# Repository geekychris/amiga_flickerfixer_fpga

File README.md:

# Amiga DENISE Flicker Fixer

An FPGA-based flicker fixer for the Commodore Amiga that reads digital RGB directly from the Super DENISE (8373 ECS) chip and outputs progressive 720p HDMI video.

**Target Platform:** Sipeed Tang Primer 20K (Gowin GW2A-LV18PG256C8/I7)

## Overview

The Amiga's native video output is 15 kHz interlaced (or non-interlaced), which most modern displays cannot accept. This flicker fixer captures the 12-bit digital RGB output from DENISE before it reaches the analog video DAC, stores fields in a DDR3 frame buffer, performs weave deinterlacing, scales the image to 720p, and outputs progressive HDMI.

Key features:
- Direct digital capture from DENISE pins (no analog conversion artifacts)
- Supports all ECS video modes: lores, hires, and superhires
- PAL and NTSC auto-detection
- Interlaced and non-interlaced mode support
- Weave deinterlacing (field merging) for flicker-free interlaced display
- Line doubling for non-interlaced modes
- Nearest-neighbor scaling to 1280x720
- 720p50 output for PAL, 720p60 for NTSC (matches source frame rate)
- Test pattern fallback when no Amiga input detected
- 128 MB DDR3 frame buffer (ping-pong per field parity)

## System Architecture

```
                        Amiga Motherboard
                        ┌──────────────┐
                        │   DENISE     │
                        │   (8373)     │
                        │              │
                        │  R[3:0] ─────┼──┐
                        │  G[3:0] ─────┼──┤
                        │  B[3:0] ─────┼──┤  12-bit digital RGB
                        │  /CSYNC ─────┼──┤  + sync/clock
                        │  /ZD    ─────┼──┤
                        │  7M     ─────┼──┤
                        │  CDAC   ─────┼──┘
                        └──────────────┘
                               │
                    ┌──────────┴──────────┐
                    │  Level Shifter      │
                    │  (74LVC245 x2)      │
                    │  5V TTL → 3.3V      │
                    └──────────┬──────────┘
                               │
┌──────────────────────────────┴──────────────────────────────┐
│                   Tang Primer 20K FPGA                       │
│                                                              │
│  ┌─────────────────┐    ┌──────────────┐    ┌────────────┐  │
│  │ denise_capture   │    │ frame_buffer │    │ output_gen │  │
│  │                  │    │    _ctrl     │    │            │  │
│  │ • 28MHz sampling │───▶│              │───▶│ • 720p     │  │
│  │ • Sync separator │    │ • DDR3      │    │   timing   │  │
│  │ • Mode detection │    │   arbiter   │    │ • Weave    │  │
│  │ • Field ID       │    │ • Ping-pong │    │   deintlc  │  │
│  │ • Pixel coords   │    │   buffers   │    │ • NN scale │  │
│  └─────────────────┘    │ • Line bufs  │    └─────┬──────┘  │
│                          └──────┬───────┘          │         │
│       ┌────────┐                │           ┌──────┴──────┐  │
│       │ Amiga  │         ┌──────┴──────┐    │  DVI_TX_Top │  │
│       │  PLL   │         │   DDR3      │    │  (Gowin IP) │  │
│       │7M→28M  │         │ Controller  │    │  TMDS enc.  │  │
│       └────────┘         │ (nand2mario │    └──────┬──────┘  │
│       ┌────────┐         │  or Gowin)  │           │         │
│       │ TMDS   │         └──────┬──────┘    ┌──────┴──────┐  │
│       │  PLL   │                │           │ HDMI Output │  │
│       │27→371M │         ┌──────┴──────┐    │ (TMDS diff) │  │
│       └────────┘         │  DDR3 SDRAM │    └─────────────┘  │
│                          │  128 MB     │                     │
│                          └─────────────┘                     │
└──────────────────────────────────────────────────────────────┘
```

### Clock Domains

| Domain | Frequency | Source | Purpose |
|--------|-----------|--------|---------|
| `I_clk` | 27 MHz | Board oscillator | System reference, DDR3 PLL input |
| `clk_28m` | ~28.38/28.64 MHz | Amiga_rPLL (4x 7M) | DENISE pixel capture |
| `clk_mem` | 100 MHz | DDR3 controller PLL | Memory access |
| `pix_clk` | 74.25 MHz | TMDS_rPLL / CLKDIV | HDMI pixel output |
| `serial_clk` | ~371.25 MHz | TMDS_rPLL | HDMI TMDS serialization |

All clock domain crossings use dual-flop synchronizers (for control signals) or async FIFOs (for data streams).

### Data Flow

```
DENISE pins (5V TTL)
    │
    ▼ (level shifted to 3.3V)
┌─────────────────────────────────────┐
│ denise_capture (28 MHz domain)      │
│ • Double-flop sync all inputs       │
│ • Sample RGB at 28 MHz              │
│ • Separate CSYNC → HSYNC + VSYNC   │
│ • Count lines → PAL/NTSC detect    │
│ • Track active area via /ZD         │
│ • Output: pixel + coords + field ID │
└──────────────┬──────────────────────┘
               ▼
        [Async FIFO 28→100 MHz]
               ▼
┌─────────────────────────────────────┐
│ frame_buffer_ctrl (100 MHz domain)  │
│ • Write pixels to DDR3 field buffer │
│ • Ping-pong buffers per parity      │
│ • Read source lines into line bufs  │
│ • Priority arbitration (read > wr)  │
└──────────────┬──────────────────────┘
               ▼
        [Line buffer BSRAM]
               ▼
┌─────────────────────────────────────┐
│ output_gen (74.25 MHz domain)       │
│ • 720p timing (50Hz or 60Hz)       │
│ • Fixed-point scale computation     │
│ • Weave deinterlace (field merge)   │
│ • 4-bit → 8-bit color expansion    │
│ • Line prefetch from frame buffer   │
└──────────────┬──────────────────────┘
               ▼
┌─────────────────────────────────────┐
│ DVI_TX_Top (Gowin encrypted IP)     │
│ • 8b/10b TMDS encoding             │
│ • OSER10 serialization              │
│ • Differential output drive         │
└──────────────┬──────────────────────┘
               ▼
         HDMI connector
```

## Module Descriptions

### `flicker_fixer_top.v` — Top Level
Instantiates all modules, manages clock generation (3 PLLs), reset sequencing, clock domain crossing for control signals, and multiplexes between Amiga video and test pattern fallback.

### `denise_capture.v` — DENISE Signal Capture
Samples DENISE's 12-bit RGB output at 28 MHz (4x the 7M clock). Includes:
- **Input synchronization**: Double-flop metastability guard on all DENISE inputs
- **Composite sync separator**: Measures /CSYNC pulse widths to distinguish normal HSYNC (~4.7 us, ~132 clocks) from equalization/serration pulses (~2.35 us, ~66 clocks) during vertical sync
- **PAL/NTSC detection**: Counts lines per field (>280 = PAL, <280 = NTSC)
- **Interlace detection**: Compares consecutive field line counts (alternating 262/263 or 312/313 = interlaced)
- **Field identification**: Long frame (extra line) = odd field, short frame = even field
- **Active area detection**: Uses /ZD (zero detect) as blanking indicator to measure active pixel width and height
- **Coordinate tracking**: Outputs pixel X/Y position within the active display area

### `frame_buffer_ctrl.v` — DDR3 Frame Buffer Arbiter
Manages DDR3 memory access for writing captured pixels and reading lines for output:
- **4 field buffers** in DDR3 (ping-pong per parity): ensures the output always reads from a completed field while capture writes to another
- **Write path**: Accepts pixels from the async FIFO, computes DDR3 addresses, issues single-word writes
- **Read path**: Prefetches entire source lines into on-chip BSRAM line buffers for zero-latency output access
- **Arbitration**: Read priority (output timing is deadline-driven) over writes

Memory map (16-bit word addresses):
```
Buffer 0 (even ping):  0x000000 + line*2048 + pixel
Buffer 1 (even pong):  0x100000 + line*2048 + pixel
Buffer 2 (odd  ping):  0x200000 + line*2048 + pixel
Buffer 3 (odd  pong):  0x300000 + line*2048 + pixel
```

Each pixel stored as 16 bits: `{4'b0, R[3:0], G[3:0], B[3:0]}`

### `output_gen.v` — HDMI Output with Deinterlacing and Scaling
Generates 720p video timing and produces scaled, deinterlaced output:
- **720p50** (1980x750, HFP=440) for PAL input
- **720p60** (1650x750, HFP=110) for NTSC input
- Both use the same 74.25 MHz pixel clock

**Weave deinterlacing**: For interlaced input, the output interleaves lines from the even and odd field buffers. Even output lines read from the even field, odd output lines from the odd field. This reconstructs the full progressive frame.

**Line doubling**: For non-interlaced input, each source line maps to two consecutive output lines.

**Nearest-neighbor scaling**: Fixed-point arithmetic maps each output pixel to source coordinates. Scale factors are recomputed at each frame start based on the detected active area dimensions.

**Line prefetch**: At the start of each output line (during horizontal blanking), the required source line is fetched from DDR3 into a line buffer. If the source line hasn't changed (repeated lines during upscaling), the fetch is skipped.

**Color expansion**: DENISE's 4-bit-per-channel color (4096 colors) is expanded to 8-bit-per-channel by bit replication: `{nibble, nibble}` maps 0x0→0x00, 0xF→0xFF.

### `async_fifo.v` — Dual-Clock FIFO
Standard gray-code pointer async FIFO for safe clock domain crossing between the 28 MHz capture domain and 100 MHz memory domain. Parameterized width and depth.

### `line_buffer.v` — Dual-Port Line Buffer
Simple dual-port RAM that infers Gowin BSRAM. Used for zero-latency line access during output pixel generation.

### `amiga_pll.v` — Amiga Clock PLL
Gowin rPLL wrapper that multiplies the 7M clock by 4 to produce the 28 MHz capture clock. VCO runs at ~448 MHz (within GW2A-18C specifications).

### `testpattern.v` — Test Pattern Generator (original)
Retained from the original HDMI demo project. Generates color bars at 720p60 as a fallback when no Amiga input is detected. Useful for verifying HDMI output works before connecting DENISE.

## DENISE (8373) Interface

### Signals to Capture

| Signal | DENISE Pin | Direction | Description |
|--------|-----------|-----------|-------------|
| R0-R3 | 20-23 | Output | Red channel (4-bit, R0=LSB) |
| B0-B3 | 24-27 | Output | Blue channel (4-bit, B0=LSB) |
| G0-G3 | 28-31 | Output | Green channel (4-bit, G0=LSB) |
| /CSYNC | 32 | Input* | Composite sync (active low) |
| /ZD | 33 | Output | Zero detect / blanking (active low) |
| CDAC | 34 | Input | Clock DAC, ~7 MHz, 90 deg from 7M (ECS only) |
| 7M | 35 | Input | 7.09/7.16 MHz pixel clock reference |

*Note: /CSYNC is an input TO DENISE (from Agnus via a buffer), but we tap the signal on the motherboard trace.

### Pin Ordering Warning

DENISE's physical pin order is R, **B**, G (not R, G, B). The blue channel (pins 24-27) sits between red and green. Verify your wiring matches the actual chip pinout.

### Pixel Clock Rates by Mode

| Mode | Pixel Rate | Pixels per 7M Cycle | Amiga Resolution |
|------|-----------|---------------------|------------------|
| Lores | ~7.09/7.16 MHz | 1 | 320 px wide |
| Hires | ~14.19/14.32 MHz | 2 | 640 px wide |
| Superhires | ~28.38/28.64 MHz | 4 | 1280 px wide |

The flicker fixer always samples at 28 MHz, capturing all modes correctly. In lores, each source pixel is sampled 4 times; in hires, 2 times; in superhires, 1 time. The scaler handles this transparently.

## Hardware Integration

### Level Shifting (Required)

DENISE outputs 5V TTL signals. The GW2A-18C FPGA is **not 5V tolerant** (3.3V LVCMOS I/O). You **must** use level shifters between DENISE and the FPGA.

Recommended:
- **74LVC245** (unidirectional, 8-bit): 2 chips covers all 16 signals
- **TXB0108** (bidirectional, 8-bit): works but unidirectional is preferred
- **Resistor divider** (1k + 2k): functional for prototyping, adds propagation delay

Wiring for 74LVC245:
```
DENISE pin ──── 74LVC245 A side (5V VCC on A side)
                74LVC245 B side (3.3V VCC on B side) ──── FPGA GPIO
                DIR = GND (A→B direction, DENISE to FPGA)
                /OE = GND (always enabled)
```

### Flying Wire Prototype

For initial prototyping:

1. Solder thin wires (30 AWG kynar/wire-wrap) to DENISE pins:
   - Pins 20-23 (R0-R3)
   - Pins 24-27 (B0-B3)
   - Pins 28-31 (G0-G3)
   - Pin 32 (/CSYNC — tap on motherboard trace)
   - Pin 33 (/ZD)
   - Pin 34 (CDAC)
   - Pin 35 (7M)
   - Pin 37 (GND)
   - Pin 19 (VCC, for level shifter 5V supply)

2. Route to a level shifter board (small perfboard with 2x 74LVC245)

3. Connect level shifter output to Tang Primer 20K GPIO header

4. Keep wires **short** (<10 cm) and **matched length** for clock and data signals to maintain timing integrity at 28 MHz

### Interposer Design (Production)

For a permanent installation, design a PCB interposer that:
- Sits between DENISE's 48-pin DIP socket and the motherboard
- Passes all 48 pins through unchanged
- Taps the 16 required signals via traces to a header/FFC connector
- Includes 74LVC245 level shifters on-board
- Routes to the FPGA via flat flex cable or pin header

The interposer only **passively observes** signals. It does not drive any DENISE bus pins. All tapped signals are outputs from DENISE (RGB, /ZD) or existing motherboard traces (/CSYNC, 7M, CDAC).

## Building

### Prerequisites

1. **Gowin EDA** (Education or Commercial edition) — [gowinsemi.com](https://www.gowinsemi.com/en/support/home/)
2. **DDR3 Controller** — one of:
   - [nand2mario/ddr3-tang-primer-20k](https://github.com/nand2mario/ddr3-tang-primer-20k) (recommended, open source, Apache 2.0)
   - Gowin DDR3 Memory Interface IP (IPUG281)

### Steps

1. Clone or download the DDR3 controller source

2. Open the Gowin IDE and create a project targeting **GW2A-LV18PG256C8/I7**

3. Add all source files:
   ```
   src/flicker_fixer_top.v    (set as top module)
   src/denise_capture.v
   src/frame_buffer_ctrl.v
   src/output_gen.v
   src/async_fifo.v
   src/line_buffer.v
   src/amiga_pll.v
   src/testpattern.v
   src/gowin_rpll/TMDS_rPLL.v
   src/dvi_tx/dvi_tx.v
   <DDR3 controller sources>
   ```

4. Add constraint files:
   ```
   src/flicker_fixer.cst      (pin assignments)
   src/flicker_fixer.sdc      (timing constraints)
   ```

5. **Regenerate PLLs** using the Gowin IP Core Generator if needed:
   - `TMDS_rPLL`: 27 MHz input, output for 720p HDMI (existing, no change needed)
   - `Amiga_rPLL`: ~7 MHz input, ~28 MHz output (4x). Verify VCO range.

6. **Uncomment the DDR3 controller instantiation** in `flicker_fixer_top.v` (search for `PLACEHOLDER`) and remove the temporary tie-off assignments below it.

7. Adjust DENISE GPIO pin assignments in `flicker_fixer.cst` to match your physical wiring.

8. Synthesize, Place & Route, program the FPGA.

### Testing Without Amiga Hardware

The design includes a test pattern fallback. When no Amiga 7M clock is detected (PLL doesn't lock), the output automatically shows color bars at 720p60. This verifies HDMI output works before connecting to DENISE.

LED indicators:

| LED | Meaning |
|-----|---------|
| LED0 | Heartbeat (~1 Hz blink) — FPGA is running |
| LED1 | Amiga input detected |
| LED2 | Amiga PLL locked (7M clock present) |
| LED3 | HDMI PLL locked |

## Supported Amiga Video Modes

| Mode | Resolution | Refresh | Output |
|------|-----------|---------|--------|
| NTSC Lores | 320x200 | 60 Hz | Line doubled, 720p60 |
| NTSC Lores Interlaced | 320x400 | 30 Hz (60 fields) | Weave deinterlaced, 720p60 |
| NTSC Hires | 640x200 | 60 Hz | Line doubled, 720p60 |
| NTSC Hires Interlaced | 640x400 | 30 Hz (60 fields) | Weave deinterlaced, 720p60 |
| PAL Lores | 320x256 | 50 Hz | Line doubled, 720p50 |
| PAL Lores Interlaced | 320x512 | 25 Hz (50 fields) | Weave deinterlaced, 720p50 |
| PAL Hires | 640x256 | 50 Hz | Line doubled, 720p50 |
| PAL Hires Interlaced | 640x512 | 25 Hz (50 fields) | Weave deinterlaced, 720p50 |
| Superhires | 1280x200/256 | 50/60 Hz | Line doubled, 720p |
| Superhires Interlaced | 1280x400/512 | 25/30 Hz | Weave deinterlaced, 720p |
| HAM6 | 320x200-512 | 50/60 Hz | Transparent (DENISE resolves HAM) |

All special modes (HAM, Extra-Halfbrite, dual playfield) are supported transparently because DENISE resolves them internally before driving the RGB pins.

## Design Details

### Memory Bandwidth Budget

| Path | Data Rate | Notes |
|------|----------|-------|
| Capture write | ~38 MB/s | 28 MHz x 16 bits x ~85% active |
| Output read | ~30 MB/s | ~800 lines x 1024 px x 2 bytes x 60 fps |
| DDR3 capacity | ~130 MB/s | 100 MHz x 16 bits x ~80% efficiency |
| **Headroom** | **~62 MB/s** | Comfortable margin |

### FPGA Resource Estimate

| Resource | Estimated | Available | Utilization |
|----------|----------|-----------|-------------|
| Logic LUTs | ~3,000 | 20,736 | ~15% |
| Registers | ~2,000 | 16,173 | ~12% |
| BSRAM | ~6 blocks | 46 | ~13% |
| rPLL | 3 | 4 | 75% |
| CLKDIV | 1 | 8 | 13% |
| OSER10 | 4 | — | — |

### Future Enhancements

- **Motion-adaptive deinterlacing**: Compare same-parity fields across frames; weave static regions, bob moving regions. Requires a third field buffer per parity (6 total).
- **Bilinear scaling**: Interpolate between source pixels for smoother upscaling.
- **Scanline emulation**: Optional darkened scanlines for CRT-like appearance.
- **OSD overlay**: On-screen display for mode info and settings.
- **Integer scaling option**: Exact 2x/3x with black borders for pixel-perfect output.
- **Audio passthrough**: Capture Amiga audio and embed in HDMI audio data island packets.

## Project Structure

```
HDMI/
├── src/
│   ├── flicker_fixer_top.v      # Top-level: clocks, CDC, mux
│   ├── denise_capture.v         # DENISE RGB + sync capture
│   ├── frame_buffer_ctrl.v      # DDR3 frame buffer arbiter
│   ├── output_gen.v             # 720p output, deinterlace, scale
│   ├── async_fifo.v             # Dual-clock FIFO (CDC)
│   ├── line_buffer.v            # Dual-port line buffer (BSRAM)
│   ├── amiga_pll.v              # 7M → 28M PLL wrapper
│   ├── testpattern.v            # Test pattern fallback (original)
│   ├── video_top.v              # Original HDMI demo top (reference)
│   ├── flicker_fixer.cst        # Pin constraints
│   ├── flicker_fixer.sdc        # Timing constraints
│   ├── dk_video.cst             # Original demo pin constraints
│   ├── dk_video.sdc             # Original demo timing constraints
│   ├── dvi_tx/
│   │   └── dvi_tx.v             # HDMI transmitter (Gowin encrypted IP)
│   └── gowin_rpll/
│       └── TMDS_rPLL.v          # TMDS clock PLL
└── impl/                        # Synthesis and P&R output
```

## References

- [Amiga Hardware Reference Manual](http://amigadev.elowar.com/read/ADCD_2.1/Hardware_Manual_guide/node0000.html) — Official Commodore documentation
- [DENISE chip specifications](https://www.amigawiki.org/lib/exe/fetch.php?media=de:parts:denise_specs.pdf) — Pin assignments and timing
- [c0pperdragon/Amiga-Digital-Video](https://github.com/c0pperdragon/Amiga-Digital-Video) — FPGA digital video for Amiga (reference design)
- [nand2mario/ddr3-tang-primer-20k](https://github.com/nand2mario/ddr3-tang-primer-20k) — DDR3 controller for this board
- [Sipeed Tang Primer 20K Wiki](https://wiki.sipeed.com/hardware/en/tang/tang-primer-20k/primer-20k.html) — Board documentation
- [Gowin GW2A-18C Datasheet](https://www.gowinsemi.com/en/product/detail/38/) — FPGA specifications

## License

This project extends the original Gowin HDMI demo. DENISE flicker fixer additions are provided as-is for educational and hobbyist use. The Gowin DVI_TX IP core is proprietary and subject to Gowin's license terms.

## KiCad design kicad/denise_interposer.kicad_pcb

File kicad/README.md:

# DENISE Interposer - KiCad Design

PCB interposer that sits between the Commodore Amiga's Super DENISE (8373) chip and its motherboard socket. Passively taps 16 video/sync signals and level-shifts them from 5V TTL to 3.3V LVCMOS for the Tang Primer 20K FPGA.

## Schematic Generation

The schematic is generated by a Python script for maintainability:

```bash
cd kicad/
python3 generate_schematic.py
```

This creates `denise_interposer.kicad_sch`. Open the `.kicad_pro` project file in KiCad 8.

## Circuit Description

### Pass-Through
All 48 DENISE DIP pins pass straight through from top socket (where DENISE plugs in) to bottom pins (which plug into the Amiga motherboard socket). The interposer is electrically invisible to the Amiga.

### Signal Taps
16 signals are tapped from the pass-through and routed to the level shifters:

| Signal Group | DENISE Pins | Level Shifter |
|-------------|-------------|---------------|
| R0-R3 (Red) | 20-23 | U1 (A1-A4) |
| B0-B3 (Blue) | 24-27 | U1 (A5-A8) |
| G0-G3 (Green) | 28-31 | U2 (A1-A4) |
| /CSYNC | 32 | U2 (A5) |
| /ZD | 33 | U2 (A6) |
| CDAC | 34 | U2 (A7) |
| 7M | 35 | U2 (A8) |

### Level Shifting
Two 74LVC245 ICs convert 5V TTL to 3.3V LVCMOS:
- Powered at 3.3V (inputs are 5V tolerant)
- DIR pin tied LOW (A-to-B direction)
- /OE pin tied LOW (always enabled)
- Each IC has a 100nF bypass capacitor

### Output Connector
J2 is a 2x10 pin header (2.54mm pitch) connecting to the FPGA:

| Pin | Signal | Pin | Signal |
|-----|--------|-----|--------|
| 1 | R0 | 2 | R1 |
| 3 | R2 | 4 | R3 |
| 5 | B0 | 6 | B1 |
| 7 | B2 | 8 | B3 |
| 9 | G0 | 10 | G1 |
| 11 | G2 | 12 | G3 |
| 13 | /CSYNC | 14 | /ZD |
| 15 | CDAC | 16 | 7M |
| 17 | +3.3V | 18 | +3.3V |
| 19 | GND | 20 | GND |

## Bill of Materials

| Ref | Value | Package | Description |
|-----|-------|---------|-------------|
| U1, U2 | 74LVC245A | TSSOP-20 | 8-bit level shifter, 5V tolerant |
| C1, C2 | 100nF | 0402 | Bypass capacitors |
| J1 | DIP-48 | Through-hole | Pass-through (socket + header pins) |
| J2 | 2x10 header | 2.54mm pitch | FPGA connection |

### 3.3V Power Supply Options
The 74LVC245s need 3.3V. Options:
1. **From FPGA board**: Supply 3.3V via J2 pins 17/18 from the Tang Primer 20K's 3.3V rail
2. **On-board LDO**: Add an AMS1117-3.3 regulator powered from DENISE's 5V (pin 19). Add input (10uF) and output (10uF) capacitors.

## PCB Layout Notes

- **DIP-48 footprint**: Use turned-pin (machined) headers for the bottom side (plugs into motherboard). Use a precision DIP socket on top (DENISE plugs in).
- **Pin spacing**: DIP-48 has 2.54mm pin pitch, 15.24mm row spacing, pins numbered counter-clockwise (1-24 on left, 25-48 on right going up).
- **Keep traces short**: Especially for 7M and CDAC clock signals. These run at ~7MHz but are used as PLL references.
- **Ground plane**: Use a ground pour on the bottom layer for signal integrity.
- **Board dimensions**: Approximately 70mm x 35mm fits the DIP-48 footprint plus level shifters and connector.

## Files

| File | Description |
|------|-------------|
| `denise_interposer.kicad_pro` | KiCad 8 project file |
| `denise_interposer.kicad_sch` | Schematic (generated) |
| `denise_interposer.kicad_pcb` | PCB with board outline |
| `generate_schematic.py` | Schematic generator script |

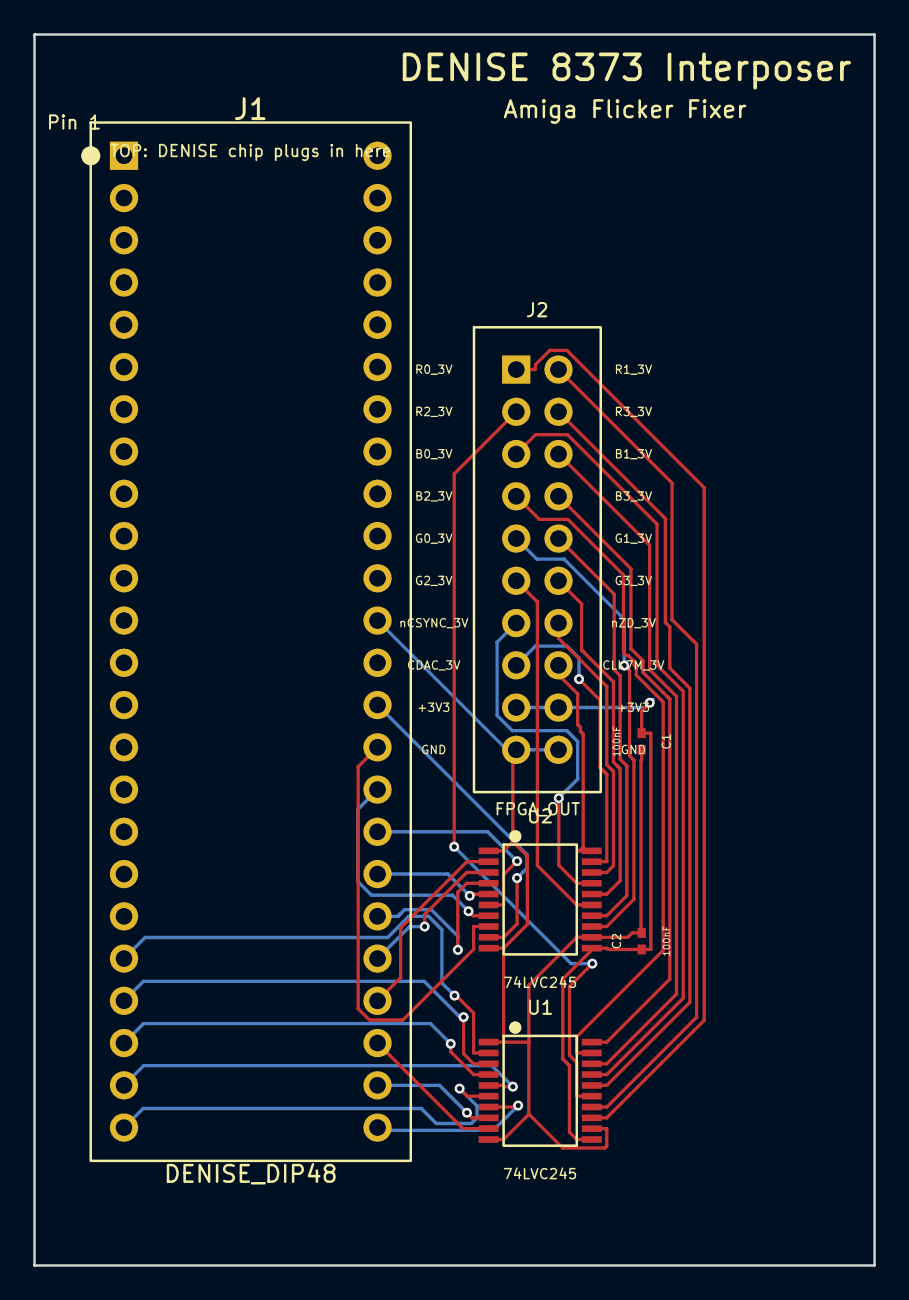
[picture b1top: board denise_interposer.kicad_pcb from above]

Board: 2 copper layers, 50.5 x 74.0 mm, 6 parts (0 on the bottom side), 34 nets.

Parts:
C1, C2: 100nF; C_0402
J1: DENISE_DIP48; DIP-48_passthrough
J2: FPGA_OUT; PinHeader_2x10
U1, U2: 74LVC245; TSSOP-20_74LVC245

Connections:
+3V3: C1.1, C2.1, J2.17, J2.18, U1.11, U2.11
B0: J1.24, U1.6
B0_3V: J2.5, U1.17
B1: J1.25, U1.7
B1_3V: J2.6, U1.18
B2: J1.26, U1.8
B2_3V: J2.7, U1.19
B3: J1.27, U1.9
B3_3V: J2.8, U1.20
CDAC: J1.34, U2.8
CDAC_3V: J2.15, U2.19
CLK7M: J1.35, U2.9
CLK7M_3V: J2.16, U2.20
G0: J1.28, U2.2
G0_3V: J2.9, U2.13
G1: J1.29, U2.3
G1_3V: J2.10, U2.14
G2: J1.30, U2.4
G2_3V: J2.11, U2.15
G3: J1.31, U2.5
G3_3V: J2.12, U2.16
GND: C1.2, C2.2, J1.37, J2.19, J2.20, U1.1, U1.10, U1.12, U2.1, U2.10, U2.12
R0: J1.20, U1.2
R0_3V: J2.1, U1.13
R1: J1.21, U1.3
R1_3V: J2.2, U1.14
R2: J1.22, U1.4
R2_3V: J2.3, U1.15
R3: J1.23, U1.5
R3_3V: J2.4, U1.16
nCSYNC: J1.32, U2.6
nCSYNC_3V: J2.13, U2.17
nZD: J1.33, U2.7
nZD_3V: J2.14, U2.18

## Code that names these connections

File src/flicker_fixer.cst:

//Copyright (C)2014-2021 Gowin Semiconductor Corporation.
//All rights reserved.
//File Title: Physical Constraints file
//GOWIN Version: 1.9.8.01
//Part Number: GW2A-LV18PG256C8/I7
//Device: GW2A-18C
//Description: Amiga DENISE Flicker Fixer - Pin Assignments
//
// IMPORTANT: DENISE signals are active 5V TTL. External level shifters
// (e.g., 74LVC245) MUST be used between DENISE and the FPGA I/O.
// The FPGA I/O is 3.3V LVCMOS and is NOT 5V tolerant.

// ==================================================================
// System clock and reset
// ==================================================================
IO_LOC "I_clk" H11;
IO_PORT "I_clk" IO_TYPE=LVCMOS33 PULL_MODE=UP;

IO_LOC "I_rst_n" T10;
IO_PORT "I_rst_n" IO_TYPE=LVCMOS33 PULL_MODE=UP;

// ==================================================================
// HDMI output (directly to HDMI connector on dock board)
// ==================================================================
IO_LOC "O_tmds_clk_p" G16,H15;
IO_PORT "O_tmds_clk_p" PULL_MODE=NONE DRIVE=3.5;
IO_LOC "O_tmds_data_p[0]" H14,H16;
IO_PORT "O_tmds_data_p[0]" PULL_MODE=NONE DRIVE=3.5;
IO_LOC "O_tmds_data_p[1]" J15,K16;
IO_PORT "O_tmds_data_p[1]" PULL_MODE=NONE DRIVE=3.5;
IO_LOC "O_tmds_data_p[2]" K14,K15;
IO_PORT "O_tmds_data_p[2]" PULL_MODE=NONE DRIVE=3.5;

// ==================================================================
// Status LEDs
// ==================================================================
IO_LOC "O_led[0]" L16;
IO_PORT "O_led[0]" IO_TYPE=LVCMOS33 PULL_MODE=UP DRIVE=8;
IO_LOC "O_led[1]" L14;
IO_PORT "O_led[1]" IO_TYPE=LVCMOS33 PULL_MODE=UP DRIVE=8;
IO_LOC "O_led[2]" N14;
IO_PORT "O_led[2]" IO_TYPE=LVCMOS33 PULL_MODE=UP DRIVE=8;
IO_LOC "O_led[3]" N16;
IO_PORT "O_led[3]" IO_TYPE=LVCMOS33 PULL_MODE=UP DRIVE=8;

// ==================================================================
// DENISE interface - GPIO header pins
// ==================================================================
// NOTE: These pin assignments use the Tang Primer 20K dock board's
// GPIO header. Adjust for your specific wiring/interposer setup.
// All pins are LVCMOS33 with internal pull-up (after level shifting).
//
// DENISE pinout reference (48-pin DIP):
//   R0-R3 = pins 20-23, G0-G3 = pins 28-31, B0-B3 = pins 24-27
//   nCSYNC = pin 32, nZD = pin 33, CDAC = pin 34, 7M = pin 35

// Red channel
IO_LOC "I_denise_r[0]" T5;
IO_PORT "I_denise_r[0]" IO_TYPE=LVCMOS33 PULL_MODE=UP;
IO_LOC "I_denise_r[1]" T4;
IO_PORT "I_denise_r[1]" IO_TYPE=LVCMOS33 PULL_MODE=UP;
IO_LOC "I_denise_r[2]" T3;
IO_PORT "I_denise_r[2]" IO_TYPE=LVCMOS33 PULL_MODE=UP;
IO_LOC "I_denise_r[3]" R5;
IO_PORT "I_denise_r[3]" IO_TYPE=LVCMOS33 PULL_MODE=UP;

// Green channel
IO_LOC "I_denise_g[0]" P6;
IO_PORT "I_denise_g[0]" IO_TYPE=LVCMOS33 PULL_MODE=UP;
IO_LOC "I_denise_g[1]" R8;
IO_PORT "I_denise_g[1]" IO_TYPE=LVCMOS33 PULL_MODE=UP;
IO_LOC "I_denise_g[2]" T8;
IO_PORT "I_denise_g[2]" IO_TYPE=LVCMOS33 PULL_MODE=UP;
IO_LOC "I_denise_g[3]" P9;
IO_PORT "I_denise_g[3]" IO_TYPE=LVCMOS33 PULL_MODE=UP;

// Blue channel
IO_LOC "I_denise_b[0]" T9;
IO_PORT "I_denise_b[0]" IO_TYPE=LVCMOS33 PULL_MODE=UP;
IO_LOC "I_denise_b[1]" R9;
IO_PORT "I_denise_b[1]" IO_TYPE=LVCMOS33 PULL_MODE=UP;
IO_LOC "I_denise_b[2]" L5;
IO_PORT "I_denise_b[2]" IO_TYPE=LVCMOS33 PULL_MODE=UP;
IO_LOC "I_denise_b[3]" L4;
IO_PORT "I_denise_b[3]" IO_TYPE=LVCMOS33 PULL_MODE=UP;

// Sync and control signals
IO_LOC "I_denise_csync_n" T6;
IO_PORT "I_denise_csync_n" IO_TYPE=LVCMOS33 PULL_MODE=UP;
IO_LOC "I_denise_zd_n" R6;
IO_PORT "I_denise_zd_n" IO_TYPE=LVCMOS33 PULL_MODE=UP;
IO_LOC "I_denise_7m" T7;
IO_PORT "I_denise_7m" IO_TYPE=LVCMOS33 PULL_MODE=NONE;
IO_LOC "I_denise_cdac" R7;
IO_PORT "I_denise_cdac" IO_TYPE=LVCMOS33 PULL_MODE=NONE;

// ==================================================================
// DDR3 memory interface
// ==================================================================
// DDR3 pin assignments are omitted until the DDR3 controller is
// integrated. The DDR3 controller module will bring its own
// constraint file with the correct pin assignments for the
// Tang Primer 20K on-board DDR3 (SK Hynix H5TQ1G63EFR).
// See: https://github.com/nand2mario/ddr3-tang-primer-20k

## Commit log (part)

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2026-04-10 flicker
